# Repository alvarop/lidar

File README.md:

# Lidar Fun

Trying out the RPLidar A1M8

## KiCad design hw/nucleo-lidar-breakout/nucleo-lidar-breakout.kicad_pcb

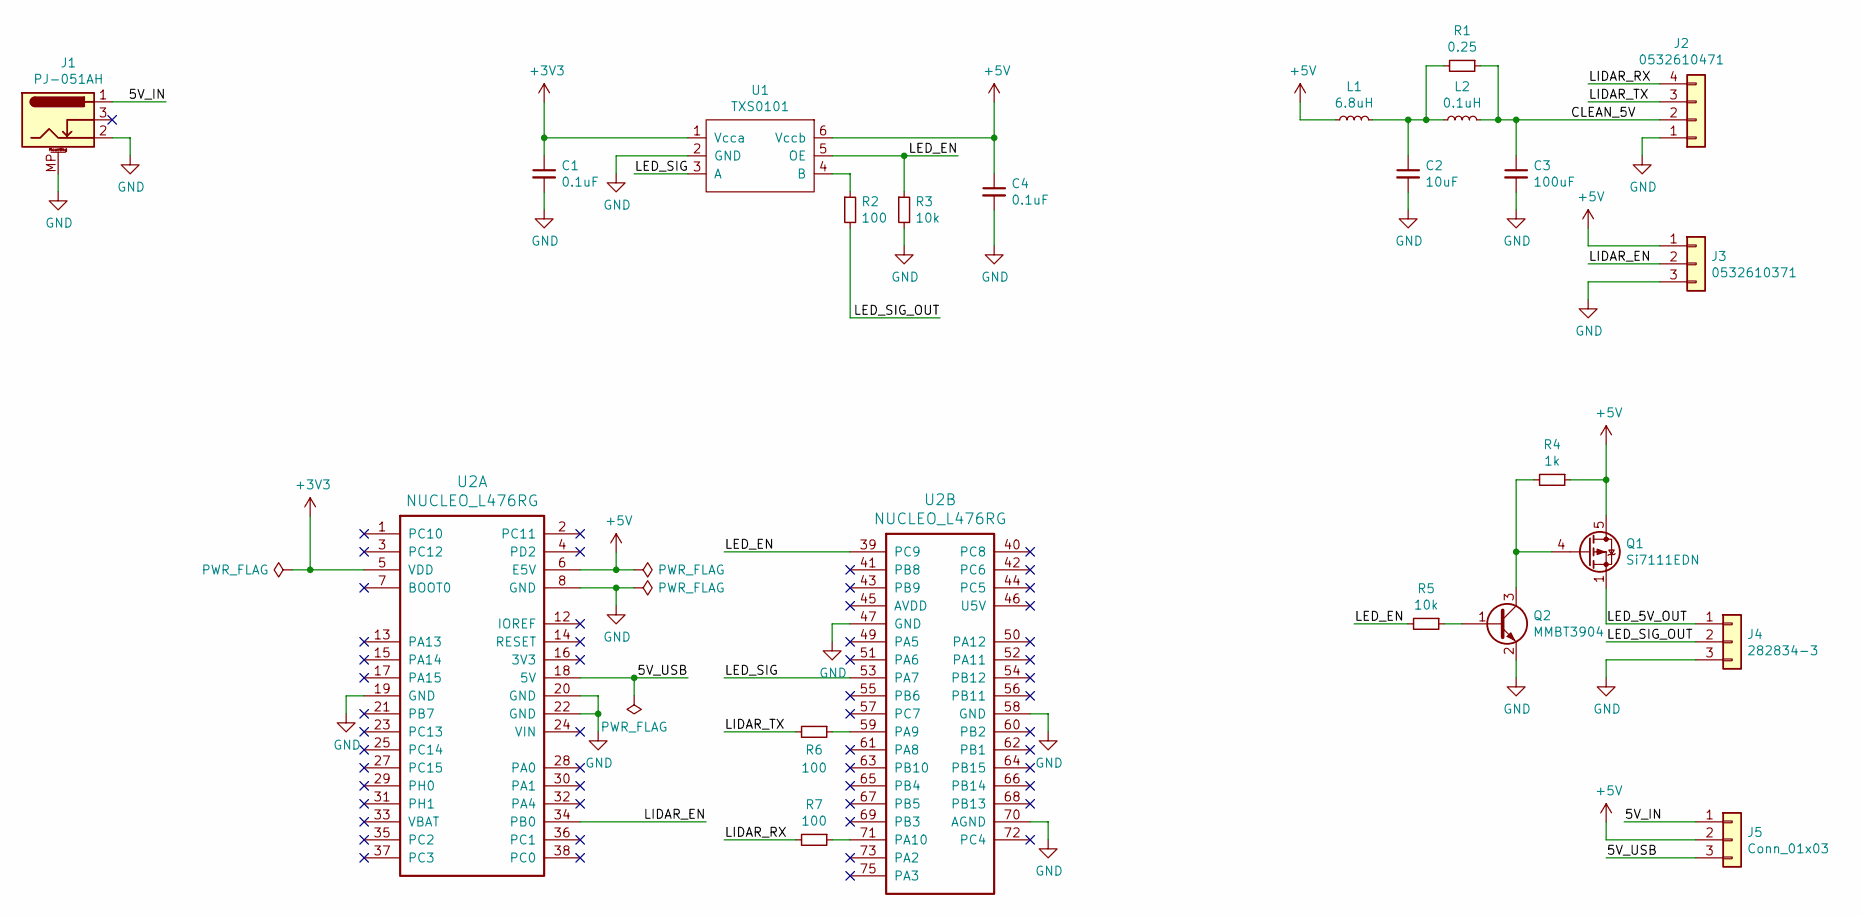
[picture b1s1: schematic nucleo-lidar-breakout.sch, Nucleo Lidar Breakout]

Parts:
C1, C4: 0.1uF; C_0402_1005Metric
C2: 10uF; C_0805_2012Metric
C3: 100uF; C_1210_3225Metric
J1: PJ-051AH
J2: ‎0532610471‎; MOLEX_0532610471
J3: ‎0532610371‎; MOLEX_0532610371
J4: 282834-3; TerminalBlock_TE_282834-3_1x03_P2.54mm_Horizontal
J5: Conn_01x03; PinHeader_1x03_P2.54mm_Vertical
L1: 6.8uH; BOURNS_SRN3015TA
L2: 0.1uH; L_0603_1608Metric
Q1: Si7111EDN; Vishay_PowerPAK_1212-8_Single
Q2: MMBT3904; SOT-23
R1: 0.25; R_0402_1005Metric
R2, R6, R7: 100; R_0402_1005Metric
R3, R5: 10k; R_0402_1005Metric
R4: 1k; R_0402_1005Metric
U1: TXS0101; TI_SC70
U2: NUCLEO_L476RG

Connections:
+3V3: C1.1, U1.1 (Vcca), U2.5 (VDD)
+5V: C4.1, J3.1, J5.2, L1.1, Q1.5 (D), R4.1, U1.6 (Vccb), U2.6 (E5V)
/5V_IN: J1.1, J5.1
/5V_USB: J5.3, U2.18 (5V)
/CLEAN_5V: C3.1, J2.2, L2.2, R1.1
/LED_5V_OUT: J4.1, Q1.1 (S), Q1.2 (S), Q1.3 (S)
/LED_EN: R3.1, R5.2, U1.5 (OE), U2.39 (PC9)
/LED_SIG: U1.3 (A), U2.53 (PA7)
/LED_SIG_OUT: J4.2, R2.2
/LIDAR_EN: J3.2, U2.34 (PB0)
/LIDAR_RX: J2.4, R7.2
/LIDAR_TX: J2.3, R6.2
GND: C1.2, C2.2, C3.2, C4.2, J1.2, J1.MP (MountPin), J2.1, J3.3, J4.3, Q2.2 (E), R3.2, U1.2 (GND), U2.8 (GND), U2.19 (GND), U2.20 (GND), U2.22 (GND), U2.47 (GND), U2.58 (GND), U2.70 (AGND)
unnamed: C2.1, L1.2, L2.1, R1.2
unnamed: Q1.4 (G), Q2.3 (C), R4.2
unnamed: Q2.1 (B), R5.1
unnamed: R2.1, U1.4 (B)
unnamed: R6.1, U2.59 (PA9)
unnamed: R7.1, U2.71 (PA10)

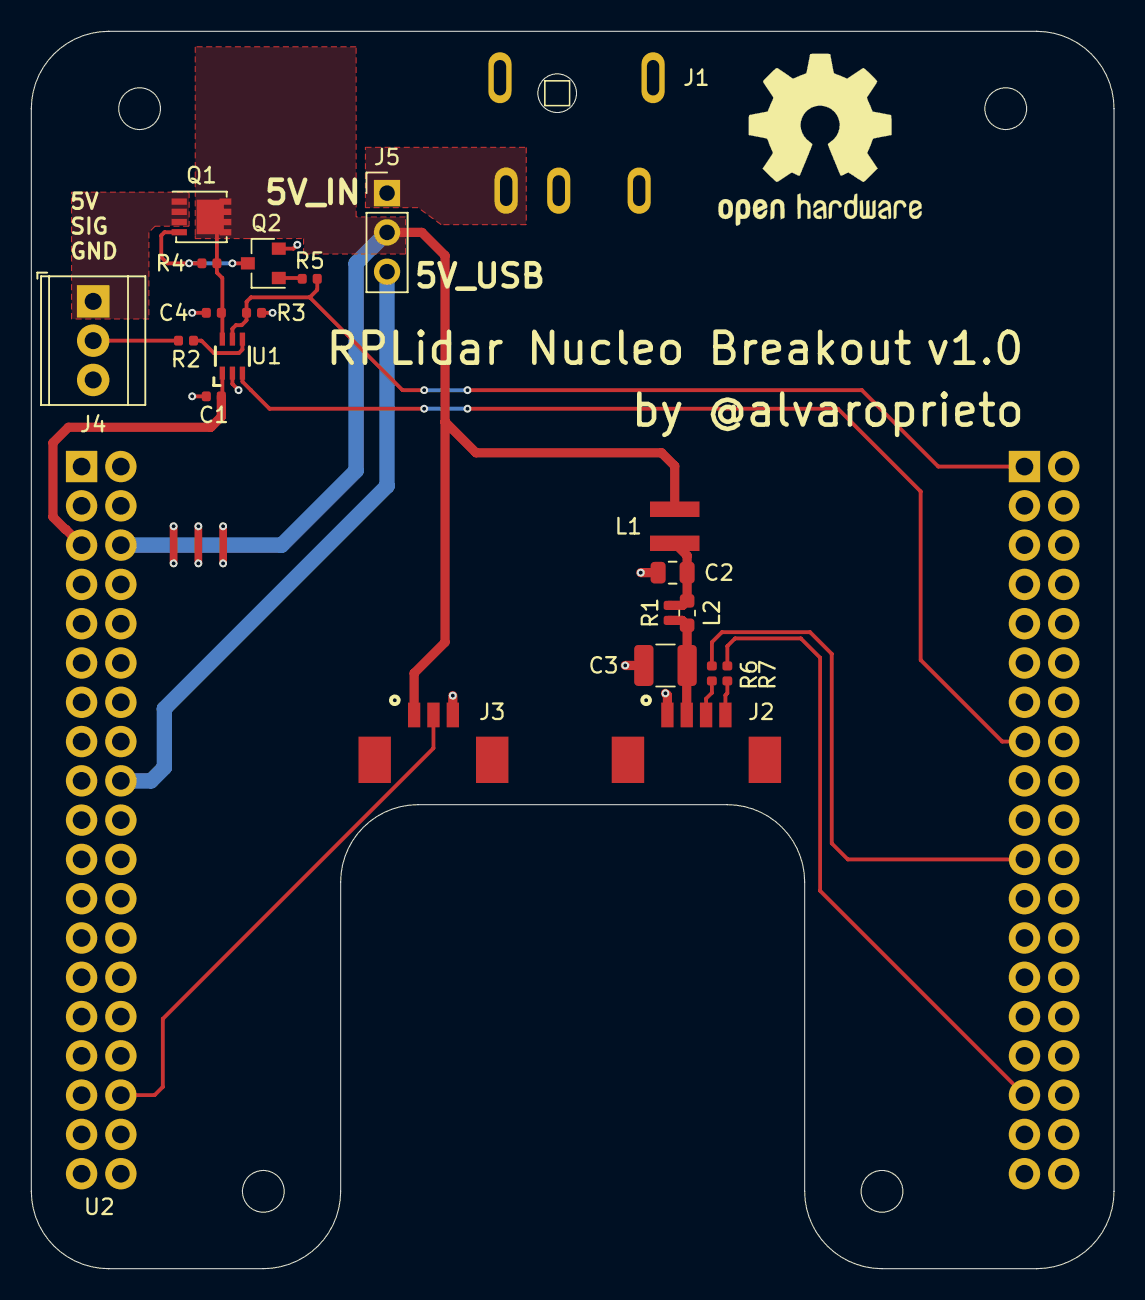
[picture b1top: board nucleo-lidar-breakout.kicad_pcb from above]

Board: 2 copper layers, 70.0 x 80.0 mm, 22 parts (0 on the bottom side), 19 nets.

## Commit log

2019-09-05 Initial commit
    WS2812 seems to work now
2019-09-07 Use more LEDS!
2019-09-07 Adding raw_uart and FIFO code
2019-09-11 Adding flush to fifo and uart
2019-09-11 Start working on rplidar code
2019-09-13 Added lots of debug but rplidar scan now working
    had to disable ws2812 writing because it disables interrupts for the
    entire SPI transaction!!!
2019-09-13 First successful visualization of lidar data :D
    RPLidar -> stm32 -> ftdi_usb -> python_gl
2019-09-14 Added SPIDMA project to get DMA SPI working ;)
    It works now!
2019-09-14 Switch to 48MHz clock for 3MHz SPI clock
    Much smaller LUT!
2019-09-14 Cleanup ws2812 code a bit
2019-09-14 Move ws2812b code to lib/driver
    Start using lights on rplidar code
2019-09-14 Adding readme
2019-09-15 Set up ws2812b with own task
2019-09-15 Minor cleanup
2019-09-16 Switch rplidar print to separate task
    Switch ws2812b drawing from task to timed callout
2019-09-19 Bringing back the last byte of zeroes
    Otherwise the spi bus sometimes idles high and ruins the next tx
2019-09-19 Added fading and upped the ws2812b refresh rate to 10ms
2019-09-28 commit old changes
2019-09-28 re-order pipfile
    re-scale gltest and add command line arg
2019-09-29 Move firmware files into fw dir
2019-09-29 Starting nucleo breakout
2019-09-29 Released rplidar nucleo breakout v1.0 to oshpark
2019-09-29 Adding hw gitignore
2019-09-29 Add part numbers to schematic
2019-10-05 adding record/playback scripts
2019-10-05 average adjacent measurements in rplidar
    Don't discard "low quality" measurements for now
2019-10-05 Don't allow overwriting files by mistake
2019-10-05 Adding lidar gl playback
2019-10-05 Don't require specific python version
2019-10-05 Nicer time printing sublack formatted python removed unused function
2019-10-05 Reduce window size and addcenter cross
2019-10-05 Updating gitignore
2019-11-01 Don't use uart for bootloader
2019-11-01 Fix lidar motor enable port
2020-03-11 misc changes
